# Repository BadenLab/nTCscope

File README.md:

<p align="right">
<h1 align="center">nTC(DBO)-Scope</h1></p>
<h4 align="center">An open source and ultra-low-cost design for large 3D field of view 2-photon microscopy</h4>
<p align="center"><h6 align="right">by F.K.Janiak and colleagues, University of Sussex, UK </h6></p>

This project is licensed under the [GNU General Public License v3.0]

Non-Telecentric 2P two-photon microscopy for 3D random access mesoscale imaging 

FK Janiak, P Bartel, R Bale, T Yoshimatsu, E Komulainen, M Zhou, K Staras, LL Prieto-Godino, T Euler, M Maravall, T Baden

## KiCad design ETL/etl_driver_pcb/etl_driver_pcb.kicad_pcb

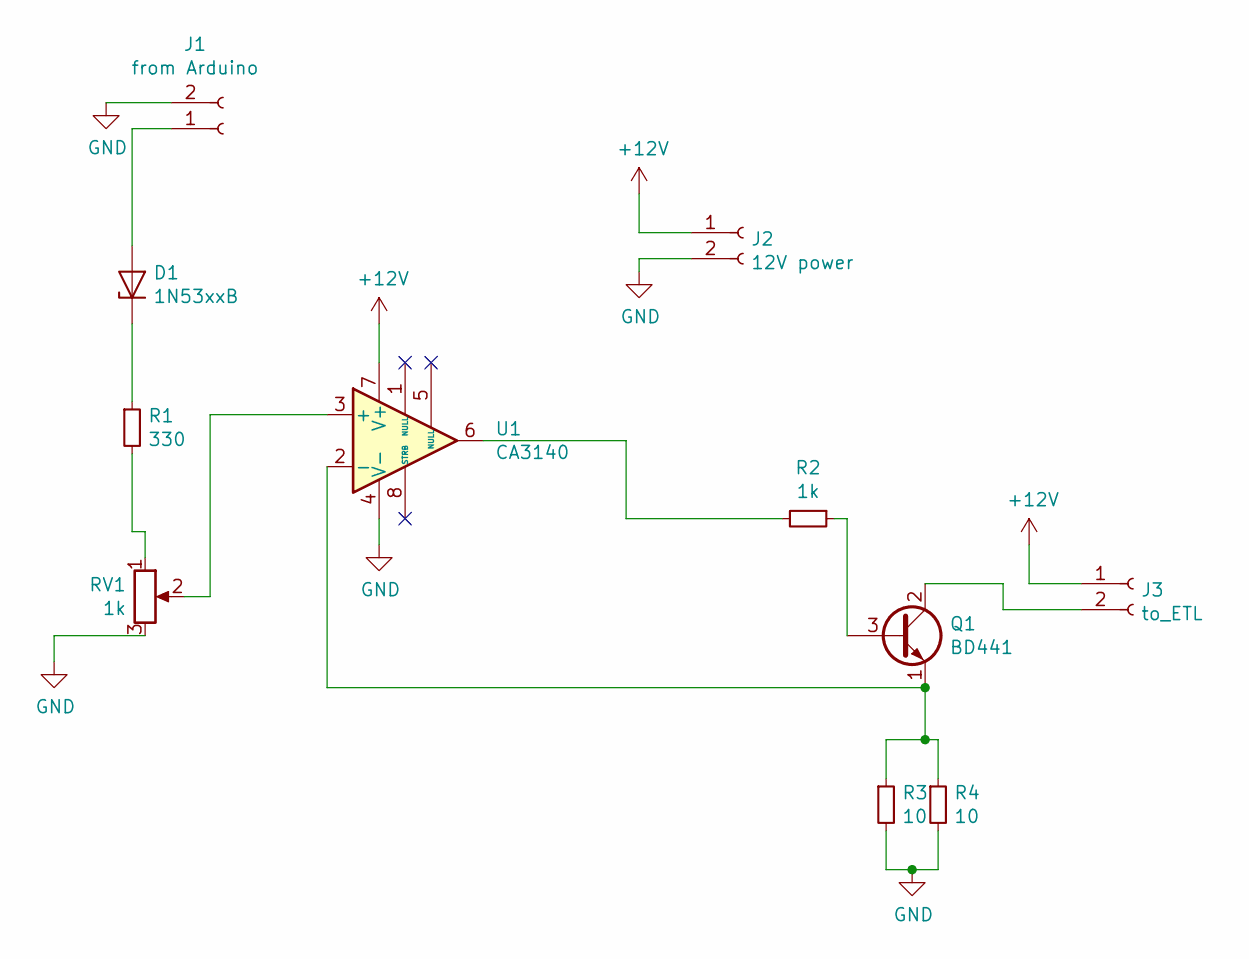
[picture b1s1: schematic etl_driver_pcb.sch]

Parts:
D1: 1N53xxB; D_DO-201_P15.24mm_Horizontal
J1: from Arduino; PinHeader_1x02_P2.54mm_Vertical
J2: 12V power; PinHeader_1x02_P2.54mm_Vertical
J3: to_ETL; PinHeader_1x02_P2.54mm_Vertical
Q1: BD441; TO-126-3_Vertical
R1: 330; R_Axial_DIN0207_L6.3mm_D2.5mm_P10.16mm_Horizontal
R2: 1k; R_Axial_DIN0207_L6.3mm_D2.5mm_P10.16mm_Horizontal
R3, R4: 10; R_Axial_DIN0207_L6.3mm_D2.5mm_P10.16mm_Horizontal
RV1: 1k; Potentiometer_ACP_CA9-H3,8_Horizontal
U1: CA3140; DIP-8_W7.62mm_Socket

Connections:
+12V: J2.1, J3.1, U1.7 (V+)
GND: J1.2, J2.2, R3.2, R4.2, RV1.3, U1.4 (V-)
unnamed: D1.1 (K), R1.1
unnamed: D1.2 (A), J1.1
unnamed: J3.2, Q1.2 (C)
unnamed: Q1.1 (E), R3.1, R4.1, U1.2 (-)
unnamed: Q1.3 (B), R2.1
unnamed: R1.2, RV1.1
unnamed: R2.2, U1.6
unnamed: RV1.2, U1.3 (+)

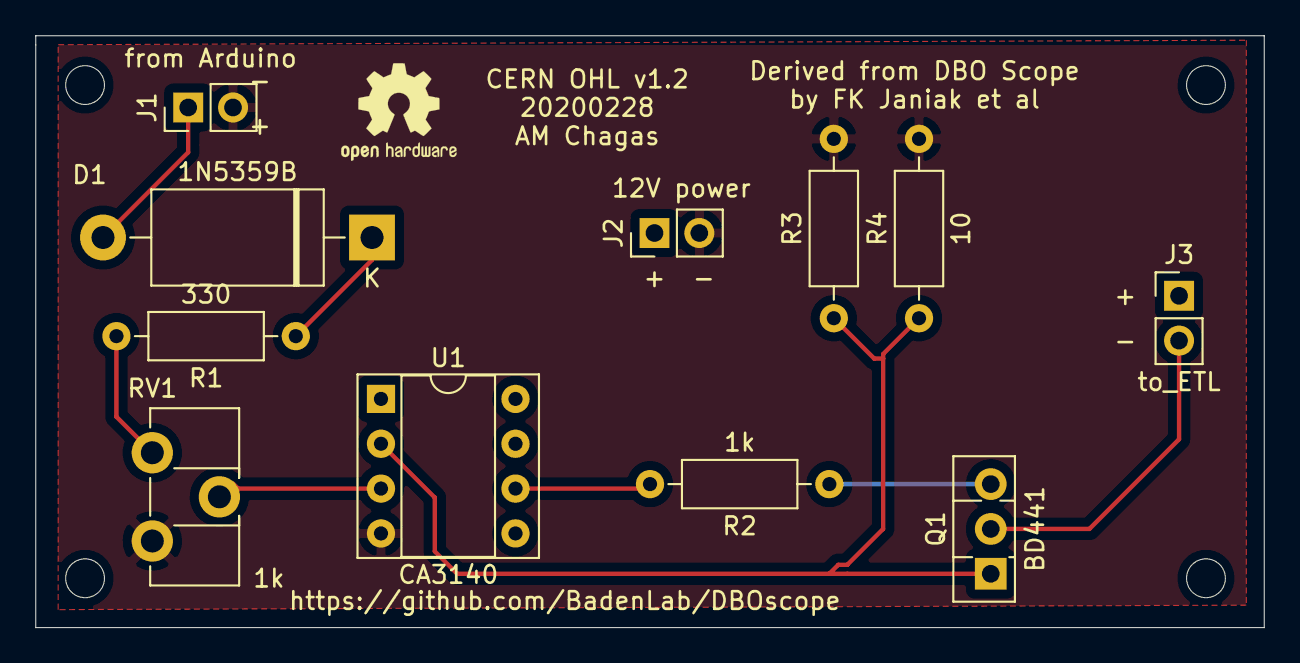
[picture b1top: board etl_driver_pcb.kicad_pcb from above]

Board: 2 copper layers, 69.6 x 33.5 mm, 11 parts (0 on the bottom side), 10 nets.

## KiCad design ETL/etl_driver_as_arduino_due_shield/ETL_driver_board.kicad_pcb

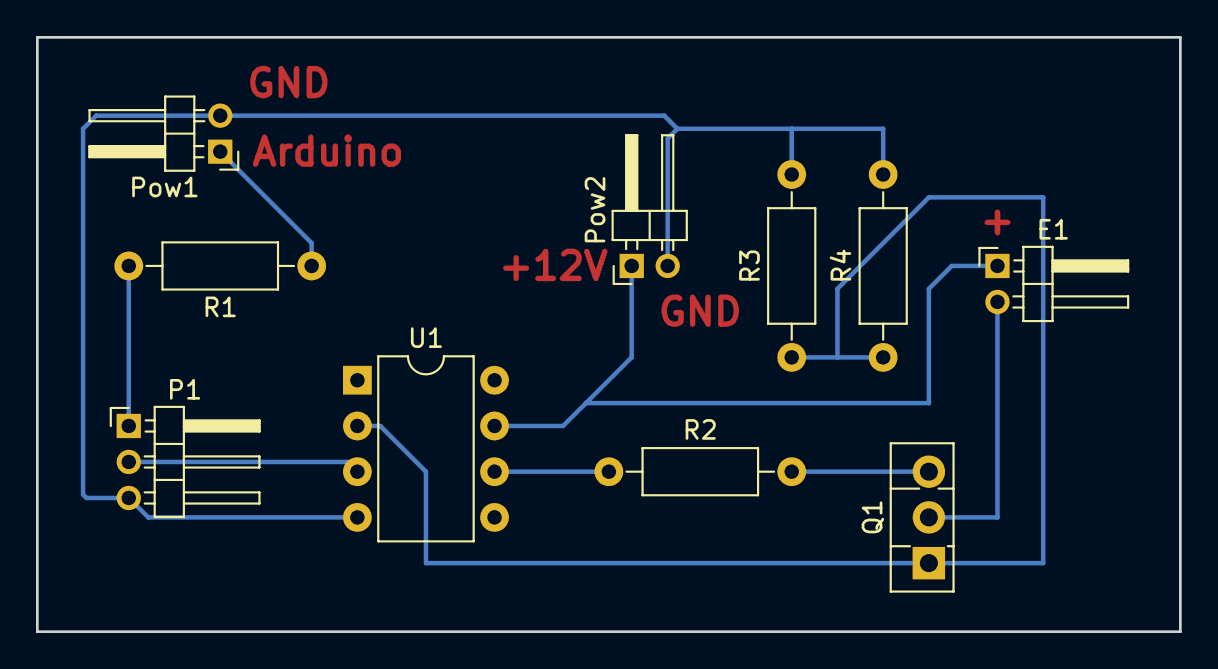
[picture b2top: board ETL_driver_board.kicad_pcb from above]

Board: 2 copper layers, 63.5 x 33.0 mm, 10 parts (0 on the bottom side), 9 nets.

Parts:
E1: ETL; Pin_Header_Angled_1x02_Pitch2.00mm
P1: potentiometer; Pin_Header_Angled_1x03_Pitch2.00mm
Pow1: Pin_Header_Angled_1x02_Pitch2.00mm
Pow2: 12Vpower; Pin_Header_Angled_1x02_Pitch2.00mm
Q1: BD441; TO-126_Vertical
R1: 330; R_Axial_DIN0207_L6.3mm_D2.5mm_P10.16mm_Horizontal
R2: 1k; R_Axial_DIN0207_L6.3mm_D2.5mm_P10.16mm_Horizontal
R3, R4: 10; R_Axial_DIN0207_L6.3mm_D2.5mm_P10.16mm_Horizontal
U1: CA3140; DIP-8_W7.62mm

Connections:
GND: P1.3, Pow1.2, Pow2.2, R3.2, R4.2, U1.4
unnamed: E1.1, Pow2.1, U1.7
unnamed: E1.2, Q1.2
unnamed: P1.1, R1.2
unnamed: P1.2, U1.3
unnamed: Pow1.1, R1.1
unnamed: Q1.1, R3.1, R4.1, U1.2
unnamed: Q1.3, R2.2
unnamed: R2.1, U1.6

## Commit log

2019-10-27 Initial upload
    Preliminary user manual and BOM
    polished version + code etc coming soon
2019-12-10 Prelim commit for manual update
2019-12-11 BOM update
2019-12-11 Clean up
2019-12-11 Update of the user manual
    includes details on the ETL driver and general updates throughout
2019-12-11 Readme and Licensce added
2019-12-11 small fix
2020-02-28 recreated PCB board in KiCad with proper production files, and started an arduino shield version
2020-04-29 Manual updates
2020-04-29 add arduino due shield for lens driver
2020-04-29 folder clean up

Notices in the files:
ETL/etl_driver_pcb/etl_driver_pcb.kicad_pcb:
CERN OHL v1.2
